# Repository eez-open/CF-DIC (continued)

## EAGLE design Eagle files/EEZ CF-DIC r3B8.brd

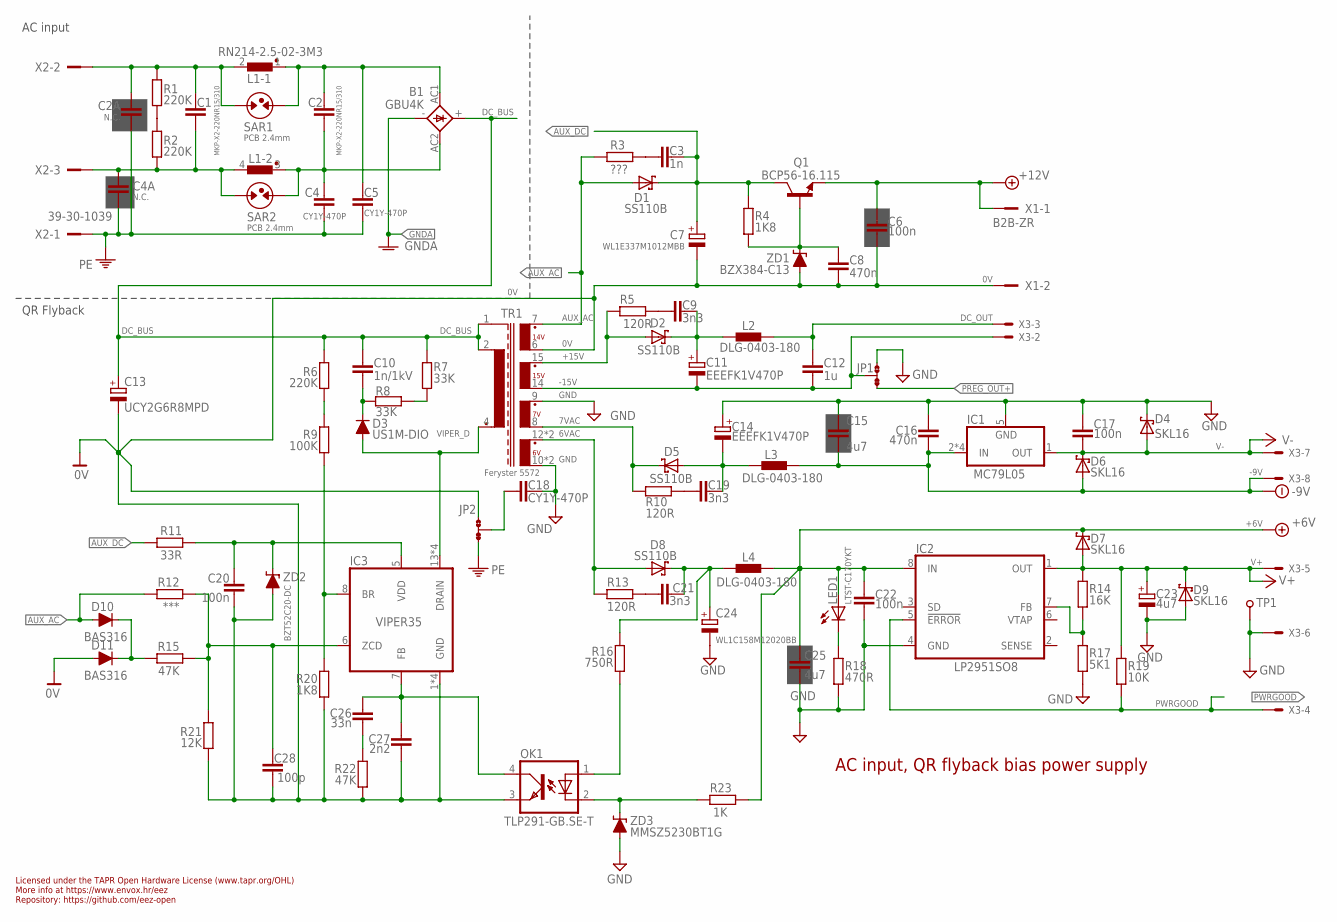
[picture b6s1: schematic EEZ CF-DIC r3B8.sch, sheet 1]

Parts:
B1: GBU4K; GBU4K_CRE
C1, C2: MKP-X2-220NR15/310; C150-072X183
C2A, C4A: N.C.; CY075-032X103
C3: 1n; C0805
C4, C5, C18: CY1Y-470P; CY075-032X103
C6, C17, C20, C22: 100n; C0603
C7: WL1E337M1012MBB; CAPAE660X610N
C8, C16: 470n; C0805
C9, C19, C21: 3n3; C0805
C10: 1n/1kV; C1210
C11, C14: EEEFK1V470P; CAPAE660X610N
C12: 1u; C0805
C13: UCY2G6R8MPD; ECAP5/10.5
C15, C25: 4u7; C1206
C23: 4u7; EC1206
C24: WL1C158M12020BB; ECAP5/10.5
C26: 33n; C0805
C27: 2n2; C0805
C28: 100p; C0805
D1, D2, D5, D8: SS110B; SMB
D3: US1M-DIO; DO214AA
D4, D6, D7, D9: SKL16; SOD123
D10, D11: BAS316; SOD323-R
IC1: MC79L05; SOIC127P600X173-8N
IC2: LP2951SO8; SOIC127P600X175-8N
IC3: VIPER35; SOIC-16
JP1, JP2: JP3-CUT
L1: RN214-2.5-02-3M3; RN214; FARNELL 1191518
L2, L3, L4: DLG-0403-180; DE0403
LED1: LTST-C170YKT; LED_0805
OK1: TLP291-GB.SE-T; SO4
Q1: BCP56-16.115; SOT230P700X180-4N
R1, R2, R6: 220K; R1206
R3: ???; R0805
R4, R20: 1K8; R0805
R5, R10, R13: 120R; R0805
R7, R8: 33K; R1210
R9: 100K; R0805
R11: 33R; R0805
R12: ***; R0805
R14: 16K; R0805
R15, R22: 47K; R0805
R16: 750R; R0805
R17: 5K1; R0805
R18: 470R; R0805
R19: 10K; R0805
R21: 12K; R0805
R23: 1K; R0805
SAR1, SAR2: PCB 2.4mm; PCB-SAR_2.4MM
TP1: PCB_TEST_TABSHIELD; PCB_SHIELD_TAB
TR1: Feryster 5572; FERYSTER_5572
X1: B2B-ZR
X2: 39-30-1039; MINIFIT_39301039_CRE
X3: 90136-1208; 70543-08
ZD1: BZX384-C13; SOD323-W
ZD2: BZT52C20-DC; SOD123
ZD3: MMSZ5230BT1G; SOD323-W

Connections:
0V: C6.2, C7.2 (-), C8.2, C13.-, C20.2, C27.2, C28.2, D11.A, IC3.1 (GND), IC3.2 (GND), IC3.3 (GND), IC3.4 (GND), JP2.NO, OK1.3 (EMIT), R20.2, R21.1, R22.2, TR1.6 (S_BIAS), X1.2, ZD1.A, ZD2.A; also elsewhere on the board
6VAC: D8.A, R13.1, TR1.12 (S1_DOT), TR1.13 (S1_DOT)
7VAC: D5.C, R10.1, TR1.8 (S2)
+6V: C22.1, C25.1, D7.C, IC2.8 (IN), L4.2, LED1.A, R23.2; also elsewhere on the board
+6V_REC: C21.2, C24.+, D8.C, L4.1, R16.1
+12V: C6.1, Q1.3 (E), X1.1; also elsewhere on the board
+15V: D2.A, R5.1, TR1.15 (S3_DOT)
+15V_REC2: C9.2, C11.1 (+), D2.C, L2.1
-7V_REC2: C14.2 (-), C19.2, D5.A, L3.1
-9V: C15.2, C16.2, D6.A, IC1.2 (IN), IC1.3 (IN), IC1.6 (IN), IC1.7 (IN), L3.2, X3.8
-15V: C11.2 (-), C12.2, JP1.COM, TR1.14 (S3), X3.2
AUX_AC: D1.A, D10.A, R3.1, R12.2, TR1.7 (S_BIAS_DOT)
AUX_DC: C3.2, C7.1 (+), D1.C, Q1.2 (C), Q1.4 (C), R4.1, R11.1
DC_BUS: B1.+, C10.1, C13.+, R6.1, R7.1, TR1.1 (SHIELD), TR1.2; also elsewhere on the board
DC_OUT: C12.1, L2.2, X3.3
FB3: OK1.2 (C), R23.1, ZD3.C
GND: C14.1 (+), C15.1, C16.1, C17.1, C18.2, C22.2, C23.-, C24.-, C25.2, D4.C, D9.A, IC1.5 (GND), IC2.4 (GND), JP1.NO, R17.2, R18.2, TP1.1, TR1.9 (S2_DOT), TR1.10 (S1), TR1.11 (S1), X3.6, ZD3.A; also elsewhere on the board
GNDA: B1.-; also elsewhere on the board
unnamed: B1.AC1, C2.1, C5.2, L1.1, SAR1.2
unnamed: B1.AC2, C2.2, C4.2, L1.3 (1), SAR2.2
unnamed: C1.1, C2A.2, L1.2, R1.1, SAR1.1, X2.2
unnamed: C1.2, C4A.2, L1.4 (2), R2.2, SAR2.1, X2.3
unnamed: R1.2, R2.1
unnamed: IC2.7 (FB), R14.2, R17.1
unnamed: C8.1, Q1.1 (B), R4.2, ZD1.C
unnamed: OK1.1 (A), R16.2
unnamed: LED1.C, R18.1
unnamed: C10.2, D3.C, R8.2
unnamed: C26.2, C27.1, IC3.7 (FB), OK1.4 (COL)
unnamed: C9.1, R5.2
unnamed: C3.1, R3.2
unnamed: C28.1, IC3.6 (ZCD), R12.1, R15.1, R21.2
unnamed: R7.2, R8.1
unnamed: C19.1, R10.2
unnamed: C21.1, R13.2
unnamed: C18.1, JP2.COM
unnamed: C26.1, R22.1
unnamed: D10.C, D11.C, R15.2
unnamed: IC3.8 (BR), R9.2, R20.1
unnamed: R6.2, R9.1
PE: C2A.1, C4.1, C4A.1, C5.1, JP2.NC, X2.1
PREG_OUT+: JP1.NC; also elsewhere on the board
PWRGOOD: IC2.5 (!ERROR), R19.2, X3.4; also elsewhere on the board
V+: C23.+, D7.A, D9.C, IC2.1 (OUT), R14.1, R19.1, X3.5; also elsewhere on the board
V-: C17.2, D4.A, D6.C, IC1.1 (OUT), X3.7; also elsewhere on the board
VIPER_D: D3.A, IC3.13 (DRAIN), IC3.14 (DRAIN), IC3.15 (DRAIN), IC3.16 (DRAIN), TR1.4 (P2_DOT)
VIPER_VDD: C20.1, IC3.5 (VDD), R11.2, ZD2.C

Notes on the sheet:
Licensed under the TAPR Open Hardware License (www.tapr.org/OHL)
Repository: https://github.com/eez-open
More info at https://www.envox.hr/eez
AC input, QR flyback bias power supply
QR Flyback
AC input

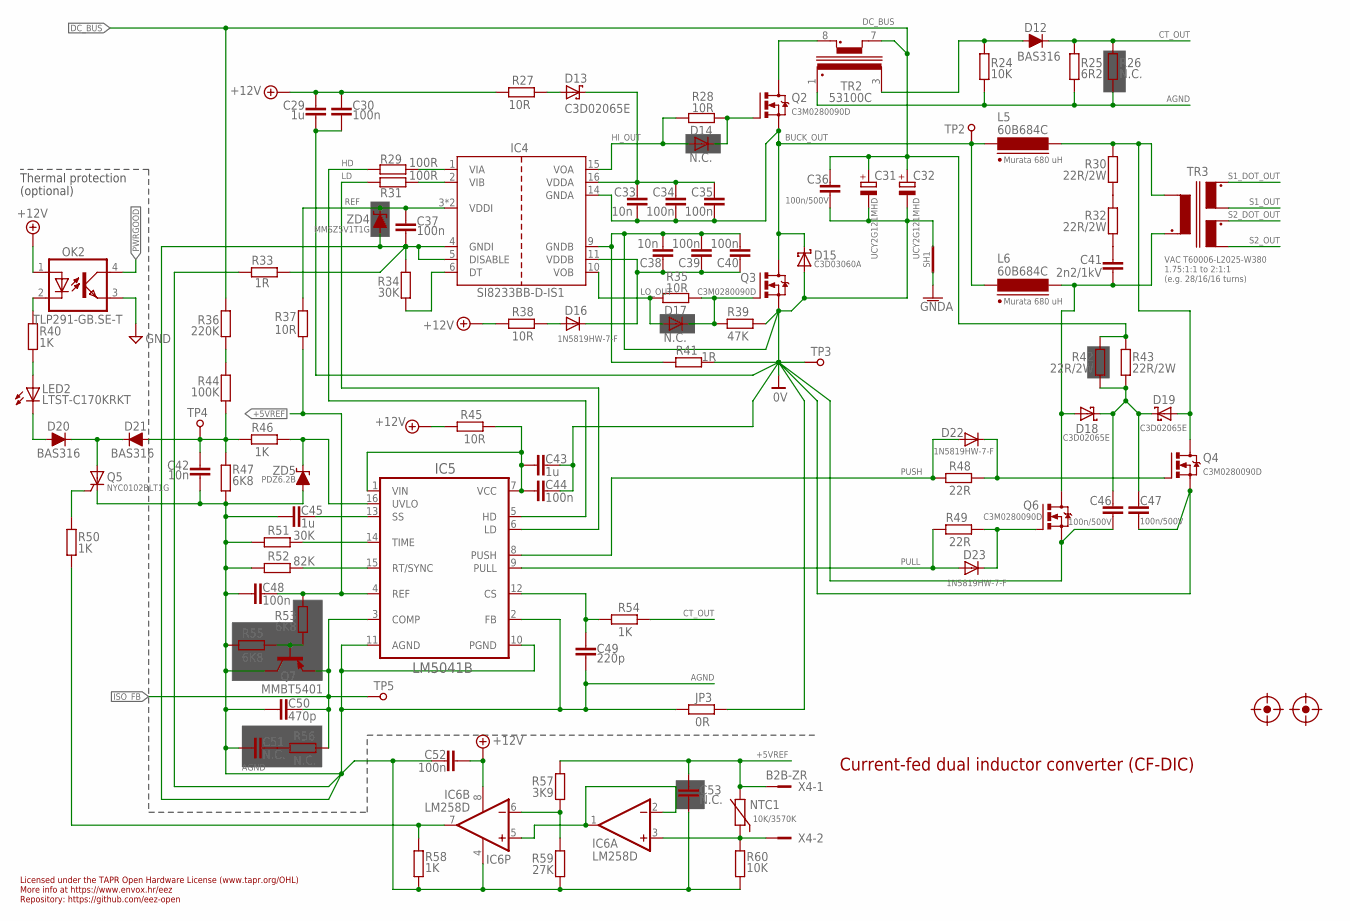
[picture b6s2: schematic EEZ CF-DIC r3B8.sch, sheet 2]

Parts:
C29, C43, C45: 1u; C0805
C30, C34, C35, C37, C39, C40, C44, C48, C52: 100n; C0603
C31, C32: UCY2G121MHD; ECAP7.5/18
C33, C38, C42: 10n; C0603
C36, C46, C47: 100n/500V; C1812
C41: 2n2/1kV; C1210
C49: 220p; C0805
C50: 470p; C0805
C51: N.C.; C0805
C53: N.C.; C0603
D12, D20, D21: BAS316; SOD323-R
D13, D18, D19: C3D02065E; TO252
D14, D17: N.C.; SOD323-W
D15: C3D03060A; TO220-2
D16, D22, D23: 1N5819HW-7-F; SOD323-W
FM1, FM2: FIDUCIAL_2; FIDUCIAL_DUAL
IC4: SI8233BB-D-IS1; SOIC-16
IC5: LM5041B; MTC16
IC6: LM258D; SOIC127P600X173-8N
JP3: 0R; R0805
L5, L6: 60B684C; MURATA_6000B
LED2: LTST-C170KRKT; LED_0805
NTC1: 10K/3570K; R_0805
OK2: TLP291-GB.SE-T; SO4
Q2, Q3, Q4, Q6: C3M0280090D; TO247BV
Q5: NYC0102BLT1G; SOT23
Q7: MMBT5401; SOT23-BEC
R24, R60: 10K; R0805
R25: 6R2; R0805
R26, R56: N.C.; R0805
R27, R28, R35, R37, R38, R45: 10R; R0805
R29, R31: 100R; R0805
R30, R32, R42, R43: 22R/2W; R2512
R33, R41: 1R; R0805
R34, R51: 30K; R0805
R36: 220K; R1206
R39: 47K; R0805
R40, R46, R50, R54, R58: 1K; R0805
R44: 100K; R0805
R47, R53, R55: 6K8; R0805
R48, R49: 22R; R0805
R52: 82K; R0805
R57: 3K9; R0805
R59: 27K; R0805
SH1: SHORTNOHOLE; SHORT_NOHOLE
TP2, TP3, TP4, TP5: PCB_TEST_TABSHIELD; PCB_SHIELD_TAB
TR2: 53100C; MURATA_5300
TR3: VAC T60006-L2025-W380; VAC_DUAL_SEC
X4: B2B-ZR
ZD4: MMSZ5V1T1G; SOD323-W
ZD5: PDZ6.2B; SOD323-W

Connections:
0V: C29.1, C30.1, C31.-, C32.-, C36.1, C38.2, C39.2, C40.2, C43.2, C44.2, C46.1, C47.1, D15.2 (A), IC4.9 (GNDB), JP3.1, Q3.S, Q4.S, Q6.S, R39.2, R41.1, R41.2, SH1.P$2 (GND_B), TP3.1; also elsewhere on the board
+5VREF: C48.2, C53.1, IC5.4 (REF), NTC1.1, R37.1, R53.1, R57.2, X4.1
+12V: C29.2, C30.2, C52.1, IC6.8 (V+), OK2.1 (A), R27.2, R38.2, R45.2; also elsewhere on the board
AGND: C37.1, C42.2, C45.1, C48.1, C49.1, C50.1, C51.1, C52.2, C53.2, IC4.4 (GNDI), IC4.5 (DISABLE), IC5.2 (FB), IC5.10 (PGND), IC5.11 (AGND), IC6.4 (V-), JP3.2, Q5.1 (C), Q7.C, R24.2, R25.2, R26.2, R33.1, R33.2, R34.1, R47.2, R51.2, R52.2, R55.2, R58.2, R59.2, R60.2, TR2.1 (S_DOT), ZD4.A, ZD5.A; also elsewhere on the board
BUCK_OUT: C33.2, C34.2, C35.2, D15.1 (C), IC4.14 (GNDA), L5.2, L6.2, Q2.S, Q3.D, TP2.1
CLAMP_C: C46.2, C47.2, D18.1 (C), D18.3 (C), D19.1 (C), D19.3 (C), R42.1, R43.1
CT_OUT: D12.C, R25.1, R26.1, R54.1
DC_BUS: C31.+, C32.+, C36.2, R36.1, R42.2, R43.2, TR2.7; also elsewhere on the board
GND: OK2.3 (EMIT); also elsewhere on the board
GNDA: SH1.P$1 (GND_A); also elsewhere on the board
HD: IC5.5 (HD), R29.2
HI_OUT: D14.A, IC4.15 (VOA), R28.2
ISO_FB: C50.2, IC5.3 (COMP), Q7.E, R56.1, TP5.1; also elsewhere on the board
LD: IC5.6 (LD), R31.2
LO_OUT: D17.A, IC4.10 (VOB), R35.1
L_PULL: C41.2, D18.2 (A), L6.1, Q6.D, TR3.P1_DOT (P_DOT)
L_PUSH: D19.2 (A), L5.1, Q4.D, R30.2, TR3.P1
unnamed: R36.2, R44.1
unnamed: C33.1, C34.1, C35.1, D13.1 (C), D13.3 (C), IC4.16 (VDDA)
unnamed: C41.1, R32.1
unnamed: IC6.3 (+IN), NTC1.2, R60.1, X4.2
unnamed: D22.C, Q4.G, R48.1
unnamed: D23.C, Q6.G, R49.1
unnamed: LED2.A, R40.2
unnamed: IC5.15 (RT/SYNC), R52.1
unnamed: D14.C, Q2.G, R28.1
unnamed: IC5.14 (TIME), R51.1
unnamed: C45.2, IC5.13 (SS)
unnamed: IC5.16 (UVLO), R46.1, ZD5.C
unnamed: IC6.6 (-IN), R57.1, R59.1
unnamed: D17.C, Q3.G, R35.2, R39.1
unnamed: D13.2 (A), R27.1
unnamed: OK2.2 (C), R40.1
unnamed: C51.2, R56.2
unnamed: IC4.1 (VIA), R29.1
unnamed: C49.2, IC5.12 (CS), R54.2
unnamed: IC6.7 (OUT), R50.2, R58.1
unnamed: IC4.2 (VIB), R31.1
unnamed: R30.1, R32.2
unnamed: IC6.1 (OUT), IC6.2 (-IN), IC6.5 (+IN)
unnamed: Q7.B, R53.2, R55.1
unnamed: IC4.6 (DT), R34.2
unnamed: D12.A, R24.1, TR2.3 (S)
unnamed: C43.1, C44.1, IC5.1 (VIN), IC5.7 (VCC), R45.1
unnamed: C38.1, C39.1, C40.1, D16.C, IC4.11 (VDDB)
unnamed: Q2.D, TR2.8 (P_DOT)
unnamed: D16.A, R38.1
unnamed: Q5.2 (G), R50.1
unnamed: D20.C, D21.C, Q5.3 (A)
unnamed: D20.A, LED2.C
PULL: D23.A, IC5.9 (PULL), R49.2
PUSH: D22.A, IC5.8 (PUSH), R48.2
PWRGOOD: OK2.4 (COL); also elsewhere on the board
REF: C37.2, IC4.3 (VDDI), IC4.8 (VDDI), R37.2, ZD4.C
S1_DOT_OUT: TR3.S1_DOT; also elsewhere on the board
S1_OUT: TR3.S1; also elsewhere on the board
S2_DOT_OUT: TR3.S2_DOT; also elsewhere on the board
S2_OUT: TR3.S2; also elsewhere on the board
ULVO: C42.1, D21.A, R44.2, R46.2, R47.1, TP4.1

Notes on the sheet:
Licensed under the TAPR Open Hardware License (www.tapr.org/OHL)
Repository: https://github.com/eez-open
More info at https://www.envox.hr/eez
Current-fed dual inductor converter (CF-DIC)
1.75:1:1 to 2:1:1
Murata 680 uH
(e.g. 28/16/16 turns)
(optional)
Thermal protection

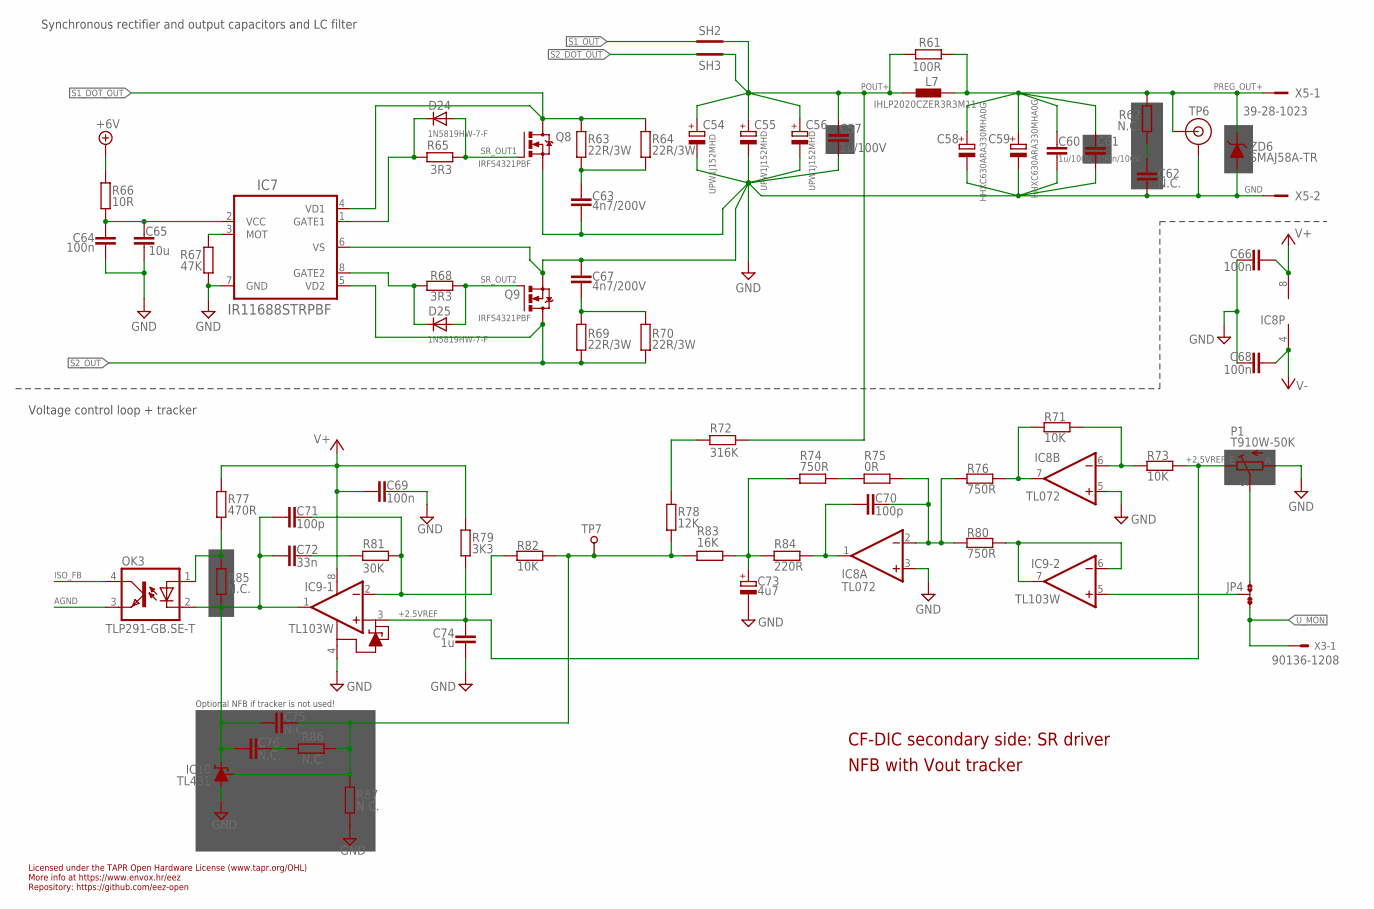
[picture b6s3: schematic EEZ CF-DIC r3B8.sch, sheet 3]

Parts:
C54, C55, C56: UPW1J152MHD; ECAP7.5/18
C57, C60: 1u/100V; C1206
C58: HHXC630ARA330MHA0G; CAPAE830X1050N; TOLERANCE ±20 %; VOLTAGERATING 63 V; MPN EEE-FK1J470P
C59: HHXC630ARA330MHA0G; CAPAE830X1050N
C61: 100n/100V; C0805
C62: N.C.; C1206
C63, C67: 4n7/200V; C1206
C64, C66, C68, C69: 100n; C0603
C65: 10u; C1210
C70, C71: 100p; C0805
C72: 33n; C0805
C73: 4u7; EC1206
C74: 1u; C0805
C75, C76: N.C.; C0805
D24, D25: 1N5819HW-7-F; SOD323-W
IC7: IR11688STRPBF; SO8
IC8: TL072; SOIC127P600X173-8N
IC9: TL103W; SOIC127P600X173-8N
IC10: TL431; SOT103P240X110-3N
JP4: JP3-CUT
L7: IHLP2020CZER3R3M11; IHLP-2020BZ-11
OK3: TLP291-GB.SE-T; SO4
P1: T910W-50K; S64W
Q8, Q9: IRFS4321PBF; TO263
R61: 100R; R0805
R62: N.C.; R1210
R63, R64, R69, R70: 22R/3W; R2512
R65, R68: 3R3; R0805
R66: 10R; R0805
R67: 47K; R0805
R71, R73, R82: 10K; R0805
R72: 316K; R0805
R74, R76, R80: 750R; R0805
R75: 0R; R0805
R77: 470R; R0805
R78: 12K; R0805
R79: 3K3; R0805
R81: 30K; R0805
R83: 16K; R0805
R84: 220R; R0805
R85, R86, R87: N.C.; R0805
SH2, SH3: SHORTNOHOLE; SHORT_NOHOLE
TP6: TEST_POINT-2; TP_1.1MM_2
TP7: PCB_TEST_TABSHIELD; PCB_SHIELD_TAB
X3: 90136-1208; 70543-08
X5: 39-28-1023; MINIFIT_5566-02A
ZD6: SMAJ58A-TR; DO214AC

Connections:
+2.5VREF: C74.1, IC9.3 (+IN1), P1.E, R73.2, R79.1
+6V: R66.1; also elsewhere on the board
AGND: OK3.3 (EMIT); also elsewhere on the board
FB: C75.2, IC10.2 (REF), R78.1, R82.2, R83.2, R86.2, R87.2, TP7.1
GND: C54.-, C55.-, C56.-, C57.2, C58.2, C59.2, C60.2, C61.2, C62.1, C63.2, C64.2, C65.2, C66.2, C67.2, C68.2, C69.2, C73.-, C74.2, IC7.6 (VS), IC7.7 (GND), IC8.3 (+IN), IC8.5 (+IN), IC9.4 (VCC-), IC10.3 (A), P1.A, Q8.2 (S), Q9.2 (S), R67.2, R87.1, TP6.GND, X5.2, ZD6.A; also elsewhere on the board
ISO_FB: OK3.4 (COL); also elsewhere on the board
unnamed: C70.2, IC8.2 (-IN), R75.2, R76.1, R80.1
unnamed: C64.1, C65.1, IC7.2 (VCC), R66.2
unnamed: C62.2, R62.1
unnamed: C72.2, R81.2
unnamed: C71.2, IC9.2 (-IN1), R81.1, R82.1
unnamed: R72.1, R78.2
unnamed: C76.2, R86.1
unnamed: IC7.3 (MOT), R67.1
unnamed: IC8.7 (OUT), R71.1, R76.2
unnamed: IC9.5 (+IN), JP4.COM
unnamed: JP4.NO, P1.S
unnamed: R74.2, R75.1
unnamed: C63.1, R63.2, R64.2
unnamed: C67.1, R69.2, R70.2
unnamed: D24.C, IC7.1 (GATE1), R65.2
unnamed: D25.C, IC7.8 (GATE2), R68.2
unnamed: C71.1, C72.1, C75.1, C76.1, IC9.1 (OUT1), IC10.1 (C), OK3.2 (C), R85.2
unnamed: IC8.6 (-IN), R71.2, R73.1
unnamed: C70.1, IC8.1 (OUT), R84.2
NFB_OFFSET: C73.+, R74.1, R83.1, R84.1
OK_A: OK3.1 (A), R77.1, R85.1
POUT+: C54.+, C55.+, C56.+, C57.1, L7.1, R61.1, R72.2, SH2.P$2 (GND_B), SH3.P$1 (GND_A)
PREG_OUT+: C58.1, C59.1, C60.1, C61.1, L7.2, R61.2, R62.2, TP6.TIP, X5.1, ZD6.C; also elsewhere on the board
S1_DOT_OUT: IC7.4 (VD1), Q8.3 (D), R63.1, R64.1; also elsewhere on the board
S1_OUT: SH2.P$1 (GND_A); also elsewhere on the board
S2_DOT_OUT: SH3.P$2 (GND_B); also elsewhere on the board
S2_OUT: IC7.5 (VD2), Q9.3 (D), R69.1, R70.1; also elsewhere on the board
SR_OUT1: D24.A, Q8.1 (G), R65.1
SR_OUT2: D25.A, Q9.1 (G), R68.1
U_MON: JP4.NC, X3.1
U_MON1: IC9.6 (-IN), IC9.7 (OUT), R80.2
V+: C66.1, C69.1, IC8.8 (V+), IC9.8 (VCC+), R77.2, R79.2; also elsewhere on the board
V-: C68.1, IC8.4 (V-); also elsewhere on the board

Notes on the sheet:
Licensed under the TAPR Open Hardware License (www.tapr.org/OHL)
Repository: https://github.com/eez-open
More info at https://www.envox.hr/eez
CF-DIC secondary side: SR driver
NFB with Vout tracker
Voltage control loop + tracker
Synchronous rectifier and output capacitors and LC filter
Optional NFB if tracker is not used!

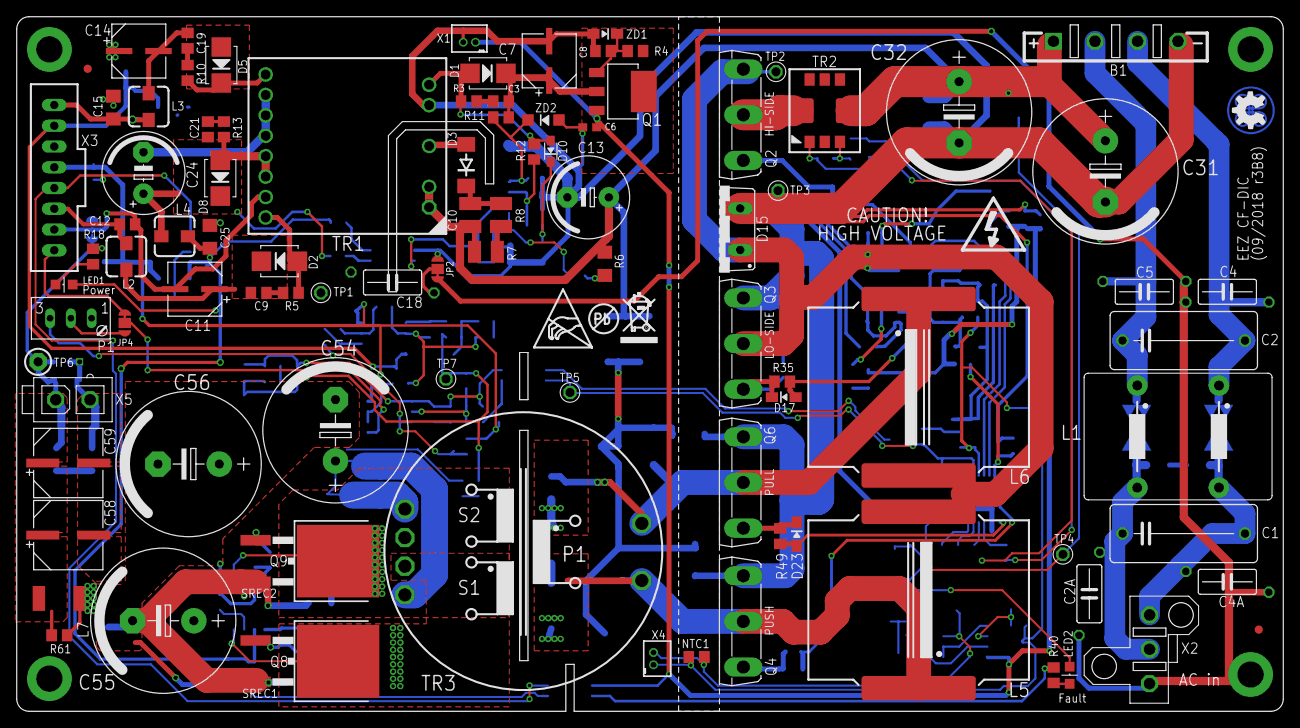
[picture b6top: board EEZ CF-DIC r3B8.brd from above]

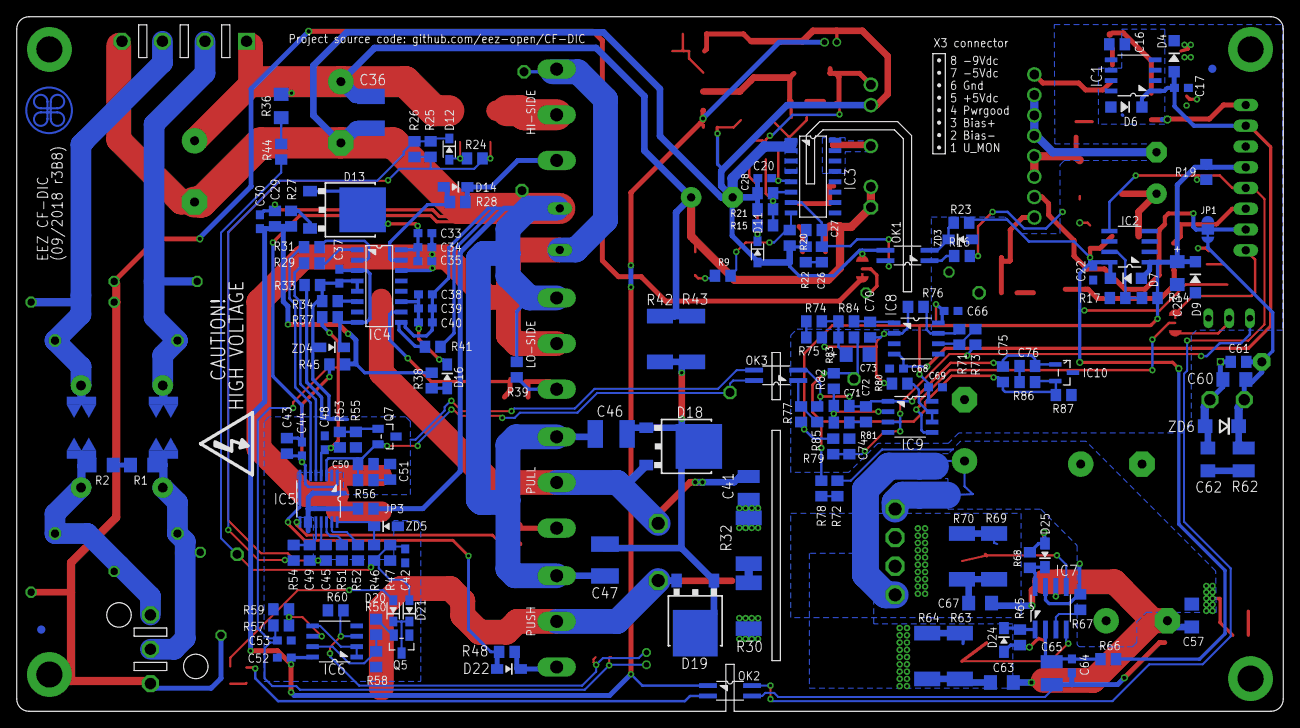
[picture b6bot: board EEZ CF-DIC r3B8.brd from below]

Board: 2 copper layers, 155.0 x 85.0 mm, 260 parts (161 on the bottom side), 128 nets.

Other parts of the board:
EEZ_SIGNATURE: SIGNATURESMALL; SIGNATURE_5MM
U$2: RECYCLE_BIN1/8
U$4: ESD_SYMBOL
U$5: PB_SMALL

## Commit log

2018-07-22 BOM and schematic preview
2018-07-22 license added
2018-07-22 Eagle and Gerber files
2018-07-22 X2 12V connector added
2018-07-22 BOM updated
2018-07-28 small changes on PCB, added alternative sync MOSFET in BOM
2018-07-28 fixed .sch - .brd inconsistency reported by Eagle 7.x
2018-07-29 BOM update, optional RC added at the output terminals
2018-07-29 modified thermals for output bulk capacitors
2018-07-30 Bridge rectifier relocated, Y2 capacitors optional positions added
2018-07-31 Optional temperature alarm
2018-07-31 New values for temp. comparator
2018-07-31 updated feature list
2018-08-22 r3B7 files without updated BOM
2018-08-26 first r3B8 version (no BOM)
2018-08-26 QR flyback schematic reorganized
2018-08-28 notice about r3B7 PCB
2018-09-14 r4B4 with updated BOM
2018-09-14 JP2 rotated
2018-09-14 README.md updated
2018-09-14 PCB parts images added
2018-09-14 PCB bottom parts image flipped horizontally
2018-09-14 Update Q1 in BOM
2018-09-15 PWRGOOD renamed to FAULT
2018-09-15 #1, power inductors rotated, shorter PUSH gate trace
2018-10-05 Sheet1of3.png fixed
2018-10-22 r5B1 without updated BOM
2018-10-22 readme.me update
2018-10-22 X2 rotated for easier cable insertion
2018-11-30 r5B5 version
2018-12-01 C4, C5, C17 value changed
2018-12-03 Mechanical drawings, optional EMI parts
2018-12-04 added block diagram
2018-12-04 block diagram filename fixed
2018-12-04 fix OTP trip note is schematics
2018-12-04 C46 increased to 2n2
2018-12-04 C46 increased to 2n2 (Eagle files)
2018-12-15 enclosure drawings
2019-01-05 r5B6 version
2019-01-05 7V secondary wiring fix
2019-01-07 BOM update
2019-01-07 new block diagram
2019-01-30 small fixes
2019-02-27 #4, #5, #6
2019-03-01 changed SR mosfets package
2019-03-03 r5B7 BOM
2019-03-03 readme.md update
2019-03-06 NFB compensation and Viper Rovp adjustment
2019-03-08 pictures update
2019-03-22 #7, #8
2019-03-22 BOM update for #7, #8
2019-03-29 new LED1 and primary side snubbers
